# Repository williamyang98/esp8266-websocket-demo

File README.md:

## Demo app using websockets

Basic ESP8266 sketch which serves a website and communicates over a websocket.
Port to work with remote pc controls project.
| Pin | Usage |
| --- | --- |
| GPIO0 | Power switch |
| GPIO2 | LED status |

Refer to ```./scripts/README.md``` for setup instructions.

## Porting to ESP-01
Modified to work with ESP-01.
- Partitions resized for 1MB flash storage.

| Partition | Old Size | New Size |
| --- | --- | --- |
| Factory | 1MB | 640kB |
| Storage | 1MB | 128kB |

- Flash command updated with resized partitions.
- Flash command uses ```DOUT``` instead of ```QIO``` for flash mode.
- ```sdkconfig``` updated with new flash storage size, flash mode, and minimum size binaries.

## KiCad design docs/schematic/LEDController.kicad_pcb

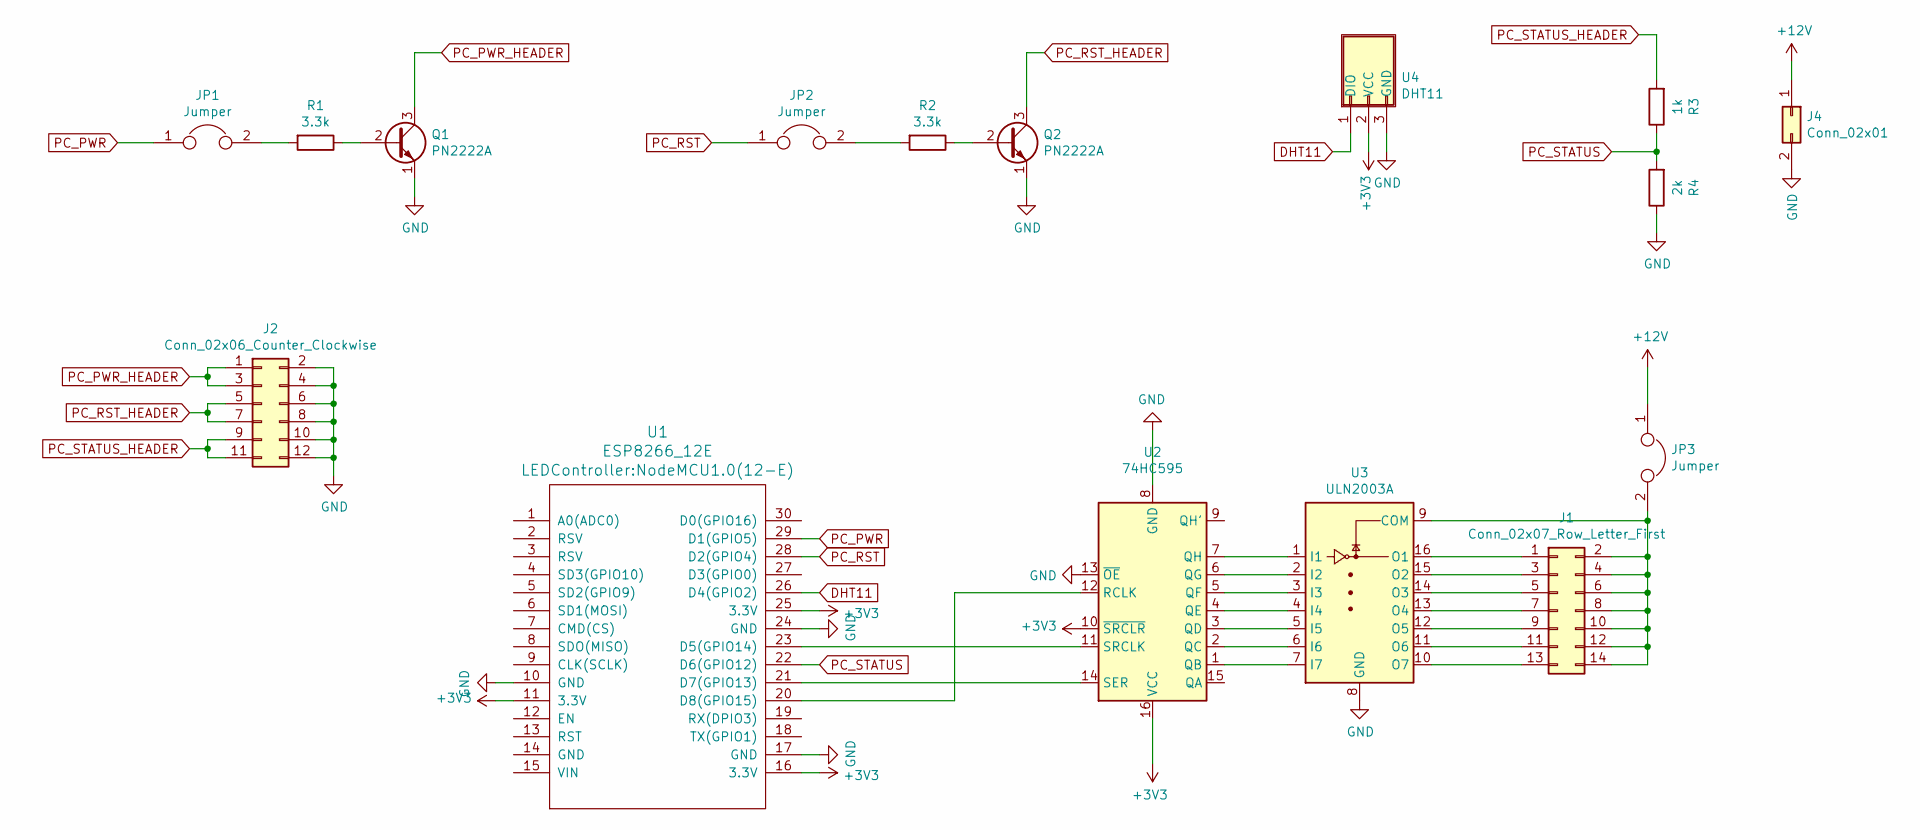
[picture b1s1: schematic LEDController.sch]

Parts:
J1: Conn_02x07_Row_Letter_First; PinHeader_2x07_P2.54mm_Vertical
J2: Conn_02x06_Counter_Clockwise; PinHeader_2x06_P2.54mm_Vertical
J4: Conn_02x01; TerminalBlock_bornier-2_P5.08mm
JP1, JP2, JP3: Jumper; PinHeader_1x02_P2.54mm_Vertical
Q1, Q2: PN2222A; TO-92_Inline_Wide
R1, R2: 3.3k; R_Axial_DIN0207_L6.3mm_D2.5mm_P10.16mm_Horizontal
R3: 1k; R_Axial_DIN0207_L6.3mm_D2.5mm_P10.16mm_Horizontal
R4: 2k; R_Axial_DIN0207_L6.3mm_D2.5mm_P10.16mm_Horizontal
U1: ESP8266_12E; NodeMCU1.0(12-E)
U2: 74HC595; DIP-16_W7.62mm_Socket
U3: ULN2003A; DIP-16_W7.62mm_Socket
U4: DHT11; PinSocket_1x03_P2.54mm_Vertical

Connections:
+3V3: U1.11 (3.3V), U1.16 (3.3V), U1.25 (3.3V), U2.10 (~SRCLR), U2.16 (VCC), U4.2 (VCC)
+12V: J4.1, JP3.1
DHT11: U1.26 (D4(GPIO2)), U4.1 (DIO)
GND: J2.2, J2.4, J2.6, J2.8, J2.10, J2.12, J4.2, Q1.1 (E), Q2.1 (E), R4.1, U1.10 (GND), U1.17 (GND), U1.24 (GND), U2.8 (GND), U2.13 (~OE), U3.8 (GND), U4.3 (GND)
unnamed: J1.1, U3.16 (O1)
unnamed: J1.3, U3.15 (O2)
unnamed: J1.5, U3.14 (O3)
unnamed: J1.7, U3.13 (O4)
unnamed: J1.9, U3.12 (O5)
unnamed: J1.2, J1.4, J1.6, J1.8, J1.10, J1.12, J1.14, JP3.2, U3.9 (COM)
unnamed: J1.11, U3.11 (O6)
unnamed: J1.13, U3.10 (O7)
unnamed: JP1.2, R1.2
unnamed: JP2.2, R2.2
unnamed: Q1.2 (B), R1.1
unnamed: Q2.2 (B), R2.1
unnamed: U1.20 (D8(GPIO15)), U2.12 (RCLK)
unnamed: U1.21 (D7(GPIO13)), U2.14 (SER)
unnamed: U1.23 (D5(GPIO14)), U2.11 (SRCLK)
unnamed: U2.1 (QB), U3.7 (I7)
unnamed: U2.2 (QC), U3.6 (I6)
unnamed: U2.3 (QD), U3.5 (I5)
unnamed: U2.4 (QE), U3.4 (I4)
unnamed: U2.5 (QF), U3.3 (I3)
unnamed: U2.6 (QG), U3.2 (I2)
unnamed: U2.7 (QH), U3.1 (I1)
PC_PWR: JP1.1, U1.29 (D1(GPIO5))
PC_PWR_HEADER: J2.1, J2.3, Q1.3 (C)
PC_RST: JP2.1, U1.28 (D2(GPIO4))
PC_RST_HEADER: J2.5, J2.7, Q2.3 (C)
PC_STATUS: R3.1, R4.2, U1.22 (D6(GPIO12))
PC_STATUS_HEADER: J2.9, J2.11, R3.2

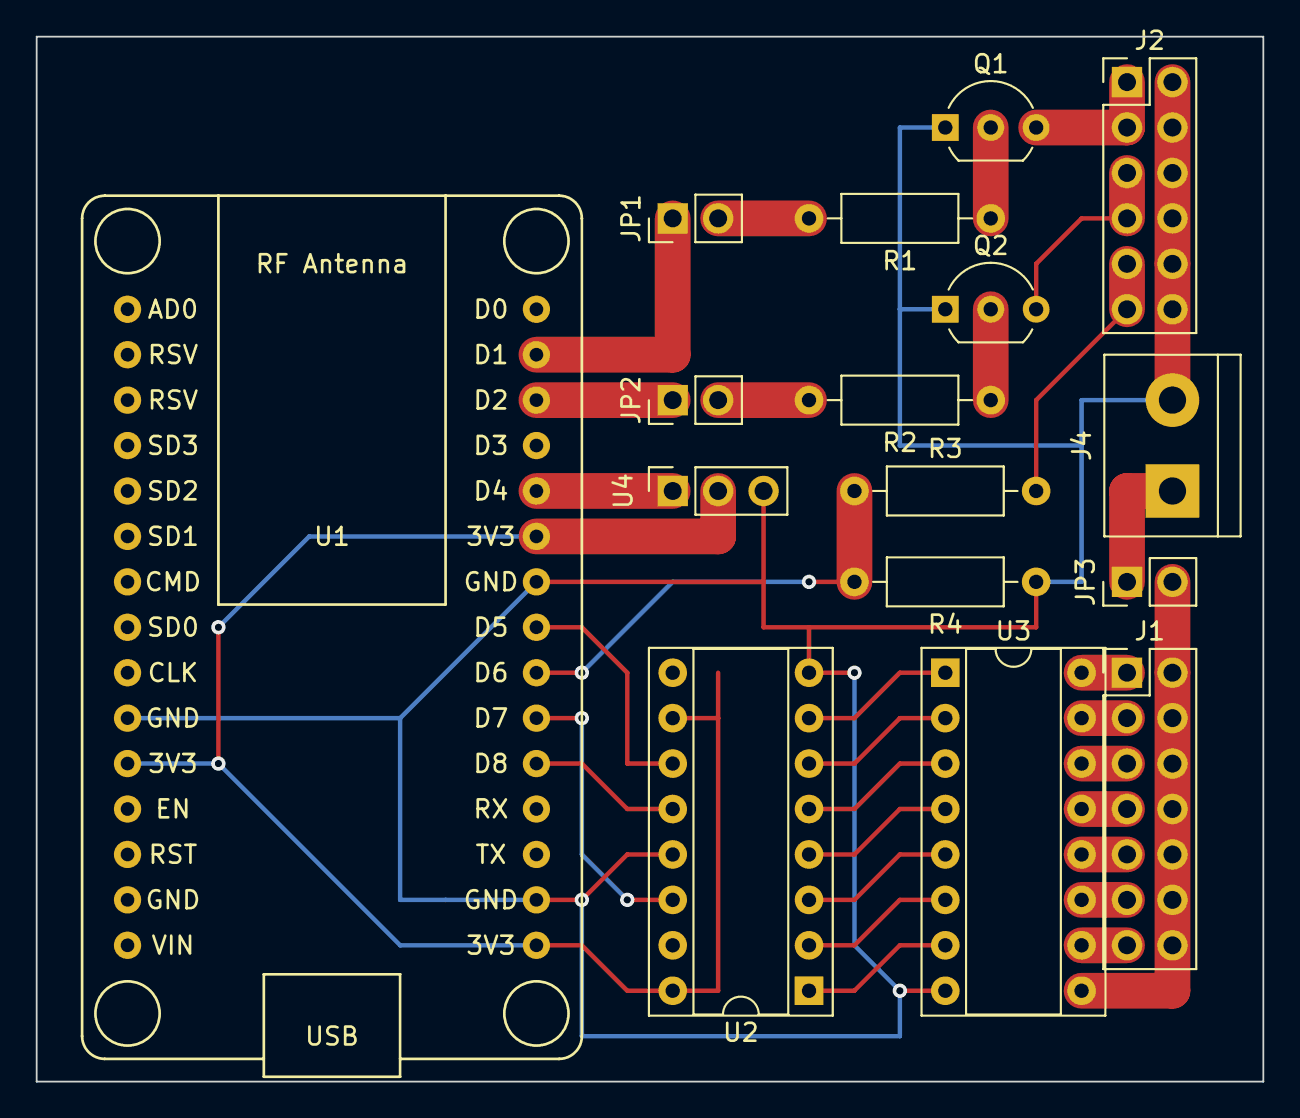
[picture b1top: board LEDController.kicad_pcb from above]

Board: 2 copper layers, 68.6 x 58.4 mm, 16 parts (0 on the bottom side), 32 nets.

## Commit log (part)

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2023-11-21 Updated serial baudrate
2023-11-22 Hacked websocket setup
2023-11-22 Rewrite with httpd_server from esp32-idf that has proper websocket implementation
2023-11-22 Updated simple demo website
2023-11-22 Cleanup
2023-11-23 Fixed scripts for linux
2023-11-23 Add note to comment out cryptography on msys2
2023-11-23 Updated demo
2023-11-24 Fixed bug where 0us wait is also considered a timeout
2023-11-24 Updated sketch to work for ESP-01
2023-11-24 Updated comment for ESP-01
2023-11-24 Added file caching using ETag header
2023-11-24 Normalise windows path separator to unix path separator
2023-12-07 Increased request header length for ipv6 clients
2023-12-18 Added nvs autosave for pwm and disabled spiffs
2024-02-13 Updated username
2024-06-26 Create tester to check if fridge is working
2024-08-18 Modified build to work with old remote pc project
